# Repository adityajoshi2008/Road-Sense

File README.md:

# Road-Sense
RoadSense is an AI-powered road safety and traffic monitoring system that uses computer vision and machine learning to detect road accidents, obstacles, potholes, lane paths, and other traffic-related hazards in real time. The system analyzes camera or dashcam footage to provide timely alerts and actionable insights, helping improve road safety .

## Features

- Road safety monitoring
- Detection of potential road hazards
- Accident or incident analysis
- Simple and efficient C-based implementation
- Easy-to-understand project structure

## Technologies Used

- C Programming Language
- GCC Compiler
- Git and GitHub

## Requirements

Before running this project, install:

- GCC compiler
- Git
- A C-compatible code editor or IDE

## Installation

Clone the repository:

```bash
git clone https://github.com/your-username/roadsense.git
```

Open the project folder:

```bash
cd roadsense
```

## Compilation

Compile the program using GCC:

```bash
gcc main.c -o roadsense
```

## Running the Program

On Linux or macOS:

```bash
./roadsense
```

On Windows:

```bash
roadsense.exe
```

## Project Status

This project is currently under development. New features and improvements may be added in the future.

## Future Improvements

- Real-time camera support
- Improved accident detection
- GPS and location tracking
- Emergency alerts
- Integration with machine-learning models
- Graphical user interface

## Contributing

Contributions, suggestions, and bug reports are welcome. Please create an issue or submit a pull request.

## License

This project is licensed under the MIT License.

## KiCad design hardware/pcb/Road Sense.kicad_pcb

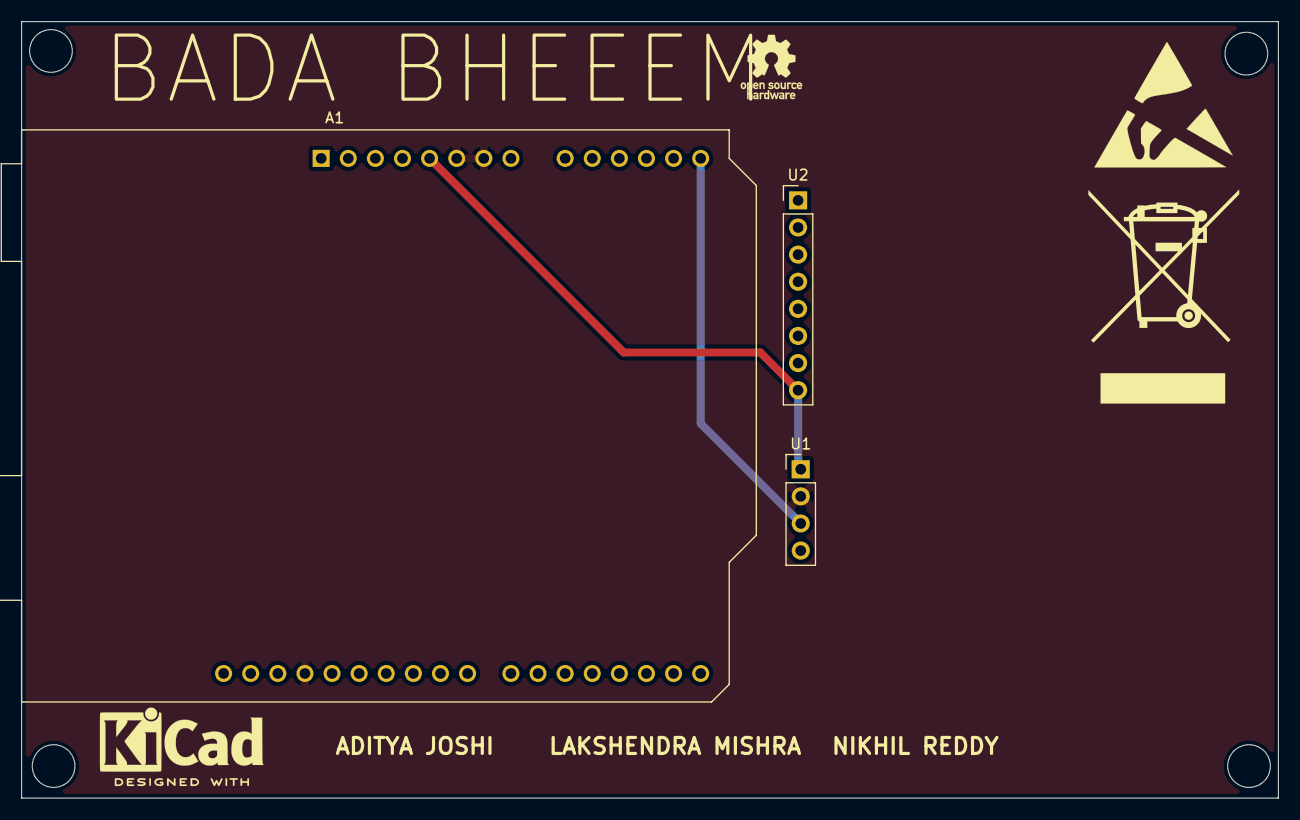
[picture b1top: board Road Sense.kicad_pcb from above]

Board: 2 copper layers, 117.8 x 72.8 mm, 3 parts (0 on the bottom side), 3 nets.

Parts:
A1: Arduino_UNO_R3
U1: PinHeader_1x04_P2.54mm_Vertical
U2: MPU-6050; PinHeader_1x08_P2.54mm_Vertical

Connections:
+5V: A1.5 (+5V), U1.1 (VCC), U2.8 (vcc_8)
GND: A1.6 (GND), A1.7 (GND), A1.29 (GND), U1.2 (GND)
unnamed: A1.14 (SCL/A5), U1.3 (SCL)
